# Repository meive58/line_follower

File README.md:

# Seguidor de Linha com ESP32

Projeto de robô seguidor de linha utilizando ESP32, sensores QTR-8 Digital, giroscópio MPU-6050 e encoders para motores N20.

## Componentes Utilizados

| Componente | Descrição |
|------------|-----------|
| ESP32 DevKit | Microcontrolador principal |
| QTR-8RC/QTR-8A | Array de 8 sensores infravermelhos para detecção de linha |
| MPU-6050 | Giroscópio e acelerômetro 6-DOF |
| Motor N20 com Encoder | Micro motor DC com encoder de quadratura |
| Ponte H (L298N/TB6612/DRV8833) | Driver para controle dos motores |

## Estrutura do Projeto

```
line_follower/
├── include/
│   └── pin_config.h        # Configuração de pinos (EDITE AQUI!)
├── lib/
│   ├── Encoder/
│   │   ├── encoder.h
│   │   └── encoder.cpp
│   ├── MotorDriver/
│   │   ├── motor_driver.h
│   │   └── motor_driver.cpp
│   ├── MPU6050/
│   │   ├── mpu6050.h
│   │   └── mpu6050.cpp
│   ├── PIDController/
│   │   ├── pid_controller.h
│   │   └── pid_controller.cpp
│   └── QTRSensor/
│       ├── qtr_sensor.h
│       └── qtr_sensor.cpp
├── src/
│   └── main.cpp            # Código principal
├── platformio.ini          # Configuração do PlatformIO
└── README.md               # Este arquivo
```

## Configuração dos Pinos

**IMPORTANTE**: Antes de compilar, edite o arquivo `include/pin_config.h` com os pinos que você escolher.

### Pinos Disponíveis no ESP32

| Pino | Recomendação |
|------|--------------|
| GPIO 0 | Evite (boot mode) |
| GPIO 1 | Evite (TX0 - debug serial) |
| GPIO 2 | LED onboard - pode usar |
| GPIO 3 | Evite (RX0 - debug serial) |
| GPIO 4 | Seguro |
| GPIO 5 | Seguro |
| **GPIO 6-11** | **NÃO USAR (flash interna)** |
| GPIO 12-33 | Seguros para uso geral |
| GPIO 34-39 | Apenas entrada (sem pull-up) |

### Exemplo de Configuração

```c
// Sensor QTR-8 (8 pinos GPIO)
#define QTR_SENSOR_0    32
#define QTR_SENSOR_1    33
#define QTR_SENSOR_2    25
#define QTR_SENSOR_3    26
#define QTR_SENSOR_4    27
#define QTR_SENSOR_5    14
#define QTR_SENSOR_6    12
#define QTR_SENSOR_7    13

// MPU-6050 (I2C)
#define MPU_SDA_PIN     21
#define MPU_SCL_PIN     22

// Encoders (4 pinos com suporte a interrupção)
#define ENCODER_LEFT_A  34
#define ENCODER_LEFT_B  35
#define ENCODER_RIGHT_A 36
#define ENCODER_RIGHT_B 39

// Motores (6 pinos)
#define MOTOR_LEFT_EN   4
#define MOTOR_LEFT_IN1  16
#define MOTOR_LEFT_IN2  17
#define MOTOR_RIGHT_EN  5
#define MOTOR_RIGHT_IN1 18
#define MOTOR_RIGHT_IN2 19

// Botões
#define BUTTON_START    23
#define BUTTON_CALIB    15
```

## Instalação

### Pré-requisitos

1. [Visual Studio Code](https://code.visualstudio.com/)
2. [Extensão PlatformIO](https://platformio.org/install/ide?install=vscode)

### Compilação e Upload

1. Abra a pasta `line_follower` no VS Code
2. Edite `include/pin_config.h` com seus pinos
3. Conecte o ESP32 via USB
4. Clique no botão "Upload" (→) na barra inferior do PlatformIO

## Uso

### Calibração

1. Ligue o robô e aguarde a inicialização
2. Pressione o botão **CALIB**
3. Mantenha o robô **imóvel** durante a calibração do giroscópio (~3s)
4. Mova o robô sobre a linha (preto e branco) por ~10 segundos
5. A calibração será salva automaticamente

### Execução

1. Posicione o robô sobre a linha
2. Pressione o botão **START**
3. Aguarde a contagem regressiva (3, 2, 1...)
4. O robô começará a seguir a linha

### LED de Status

| Estado | LED |
|--------|-----|
| Aguardando | Pisca lento (1Hz) |
| Calibrando | Aceso fixo |
| Seguindo | Aceso fixo |
| Linha perdida | Pisca rápido (10Hz) |

## Ajuste do PID

Os ganhos do PID estão definidos no arquivo `src/main.cpp`:

```c
#define PID_KP  0.1f    // Proporcional
#define PID_KI  0.0001f // Integral
#define PID_KD  0.5f    // Derivativo
```

### Guia de Ajuste

1. **Comece com Ki = 0, Kd = 0**
2. **Aumente Kp** até o robô oscilar levemente
3. **Aumente Kd** para reduzir a oscilação
4. **Adicione Ki** (pequeno) se houver erro persistente

### Valores Sugeridos para Início

| Pista | Kp | Ki | Kd |
|-------|----|----|----| 
| Iniciante (curvas suaves) | 0.05 | 0.0001 | 0.3 |
| Intermediário | 0.1 | 0.0002 | 0.5 |
| Avançado (curvas fechadas) | 0.15 | 0.0005 | 0.8 |

## Diagrama de Conexões

```
                    ┌─────────────────┐
                    │     ESP32       │
                    └─────────────────┘
                            │
        ┌───────────────────┼───────────────────┐
        │                   │                   │
        ▼                   ▼                   ▼
┌───────────────┐   ┌───────────────┐   ┌───────────────┐
│   QTR-8       │   │   MPU-6050    │   │   Ponte H     │
│   (8 pinos)   │   │   (I2C)       │   │   (6 pinos)   │
└───────────────┘   └───────────────┘   └───────────────┘
                                                │
                                        ┌───────┴───────┐
                                        │               │
                                        ▼               ▼
                                ┌───────────┐   ┌───────────┐
                                │ Motor E   │   │ Motor D   │
                                │ + Encoder │   │ + Encoder │
                                └───────────┘   └───────────┘
```

## API dos Módulos

### QTRSensorArray

```cpp
void calibrate();                    // Calibra os sensores
uint16_t readLinePosition();         // Retorna posição (0-7000)
int16_t getError();                  // Retorna erro (-3500 a +3500)
bool isLineLost();                   // Verifica se perdeu a linha
bool detectCrossing();               // Detecta cruzamento
```

### MPU6050Sensor

```cpp
void calibrateGyro(uint16_t samples); // Calibra o giroscópio
void update();                        // Atualiza ângulos (chamar no loop)
float getYaw();                       // Retorna ângulo yaw em graus
void resetYaw();                      // Reseta yaw para zero
```

### Encoder

```cpp
long getCount();                     // Retorna contagem de pulsos
float getRPM();                      // Retorna velocidade em RPM
float getDistance(float diameter);   // Retorna distância percorrida
void resetCount();                   // Reseta contador
```

### MotorDriver

```cpp
void setSpeeds(int16_t left, int16_t right);  // Define velocidades
void forward(uint8_t speed);                   // Move para frente
void brake();                                  // Freia os motores
```

## Solução de Problemas

| Problema | Solução |
|----------|---------|
| ESP32 não conecta | Verifique o driver USB (CP210x ou CH340) |
| Sensores não calibram | Verifique as conexões e alimentação |
| Robô não segue a linha | Recalibre em ambiente adequado (iluminação constante) |
| Robô oscila muito | Reduza Kp ou aumente Kd |
| Robô perde a linha nas curvas | Aumente a velocidade base ou ajuste Kp |
| Motores não funcionam | Verifique alimentação da ponte H |

## Licença

Este projeto é livre para uso educacional.

## Autor

Desenvolvido como projeto de TCC.

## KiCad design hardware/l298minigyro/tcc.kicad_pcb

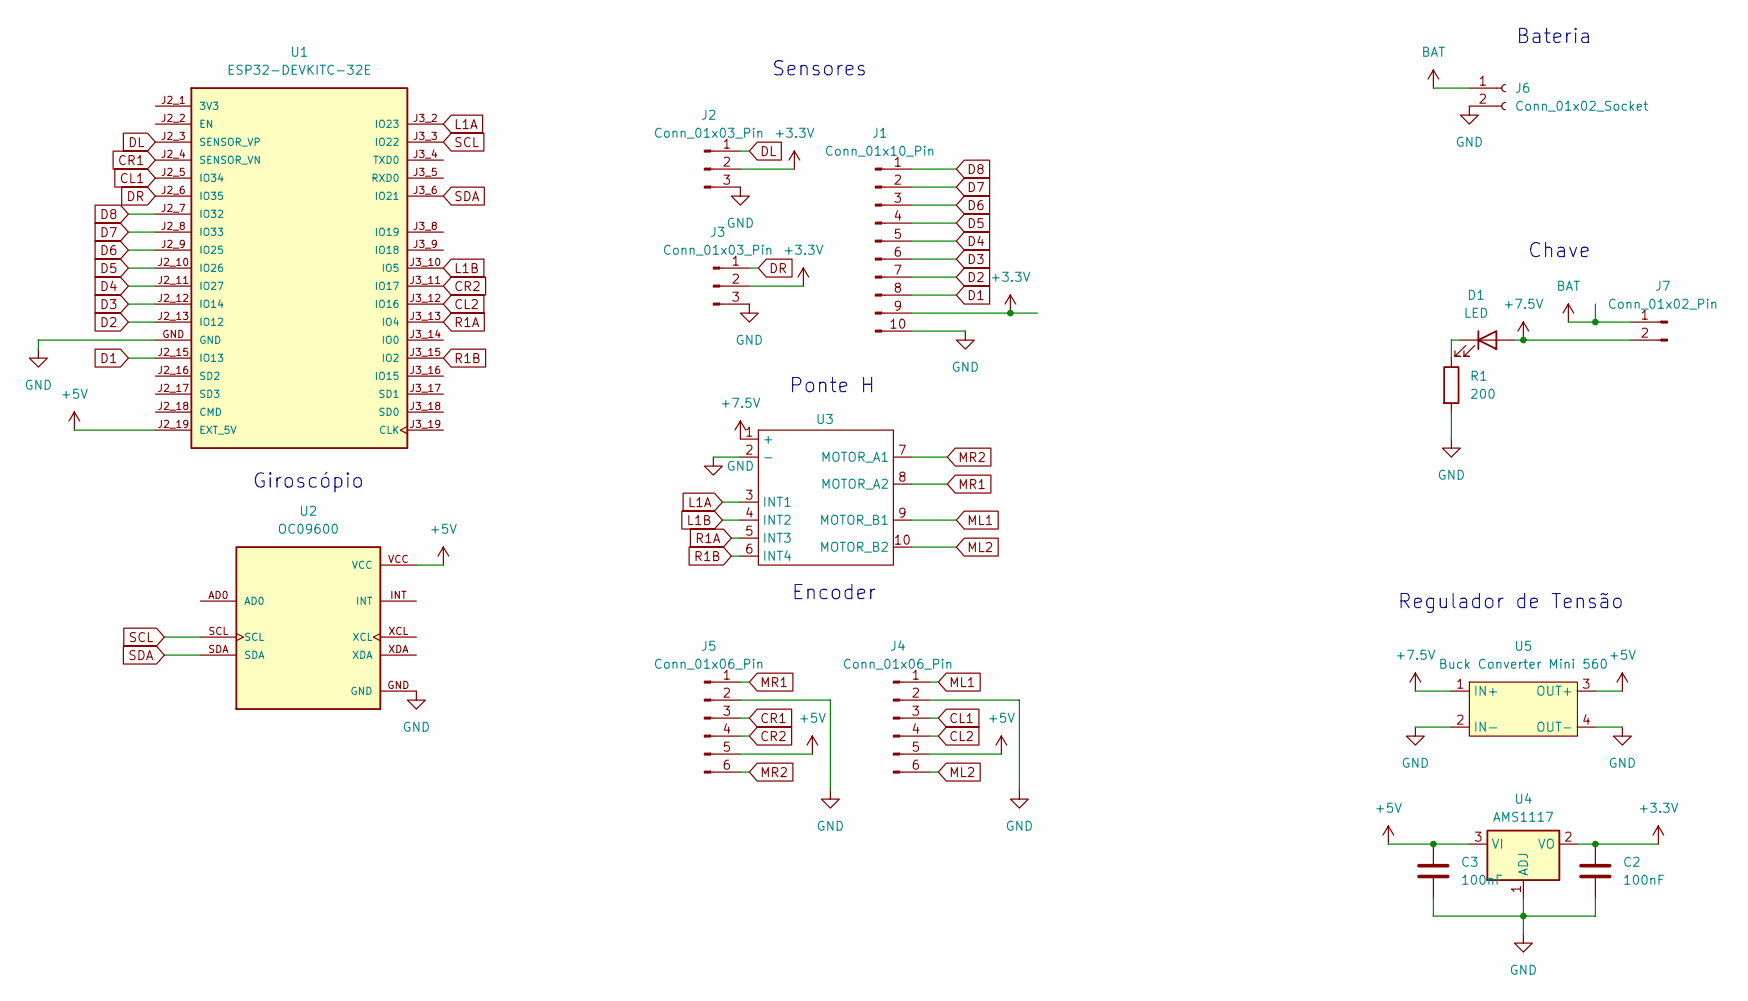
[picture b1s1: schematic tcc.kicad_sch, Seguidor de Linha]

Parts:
C2, C3: 100nF; C_Disc_D4.7mm_W2.5mm_P5.00mm
D1: LED; LED_D5.0mm
J1: Conn_01x10_Pin; PinHeader_1x10_P2.54mm_Vertical
J2, J3: Conn_01x03_Pin; PinHeader_1x03_P2.54mm_Vertical
J4, J5: Conn_01x06_Pin; JST_PH_B6B-PH-K_1x06_P2.00mm_Vertical
J6: Conn_01x02_Socket; PinSocket_1x02_P1.27mm_Vertical_SMD_Pin1Left
J7: Conn_01x02_Pin; PinHeader_1x02_P2.54mm_Vertical
R1: 200; R_Axial_DIN0204_L3.6mm_D1.6mm_P7.62mm_Horizontal
U1: ESP32-DEVKITC-32E; MODULE_ESP32-DEVKITC-32E; PARTREV 1.4
U2: OC09600; MODULE_OC09600; PARTREV NA
U3: H-Bridge-MX1616-Module
U4: AMS1117; SOT-223-3_TabPin2
U5: Buck Converter Mini 560; Mini_560

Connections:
+3.3V: C2.1, J1.9, J2.2, J3.2, U4.2 (VO)
+5V: C3.1, J4.5, J5.5, U1.J2_19 (EXT_5V), U2.VCC, U4.3 (VI), U5.3 (OUT+)
+7.5V: D1.2 (A), J7.2, U3.1 (+), U5.1 (IN+)
BAT: J6.1, J7.1
CL1: J4.3, U1.J2_5 (IO34)
CL2: J4.4, U1.J3_12 (IO16)
CR1: J5.3, U1.J2_4 (SENSOR_VN)
CR2: J5.4, U1.J3_11 (IO17)
D1: J1.8, U1.J2_15 (IO13)
D2: J1.7, U1.J2_13 (IO12)
D3: J1.6, U1.J2_12 (IO14)
D4: J1.5, U1.J2_11 (IO27)
D5: J1.4, U1.J2_10 (IO26)
D6: J1.3, U1.J2_9 (IO25)
D7: J1.2, U1.J2_8 (IO33)
D8: J1.1, U1.J2_7 (IO32)
DL: J2.1, U1.J2_3 (SENSOR_VP)
DR: J3.1, U1.J2_6 (IO35)
GND: C2.2, C3.2, J1.10, J2.3, J3.3, J4.2, J5.2, J6.2, R1.2, U1.GND, U2.GND, U3.2 (-), U4.1 (ADJ), U5.2 (IN-), U5.4 (OUT-)
L1A: U1.J3_2 (IO23), U3.3 (INT1)
L1B: U1.J3_10 (IO5), U3.4 (INT2)
ML1: J4.1, U3.9 (MOTOR_B1)
ML2: J4.6, U3.10 (MOTOR_B2)
MR1: J5.1, U3.8 (MOTOR_A2)
MR2: J5.6, U3.7 (MOTOR_A1)
unnamed: D1.1 (K), R1.1
R1A: U1.J3_13 (IO4), U3.5 (INT3)
R1B: U1.J3_15 (IO2), U3.6 (INT4)
SCL: U1.J3_3 (IO22), U2.SCL
SDA: U1.J3_6 (IO21), U2.SDA

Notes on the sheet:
Encoder
Regulador de Tensão
Sensores
Chave
Giroscópio
Bateria
Ponte H

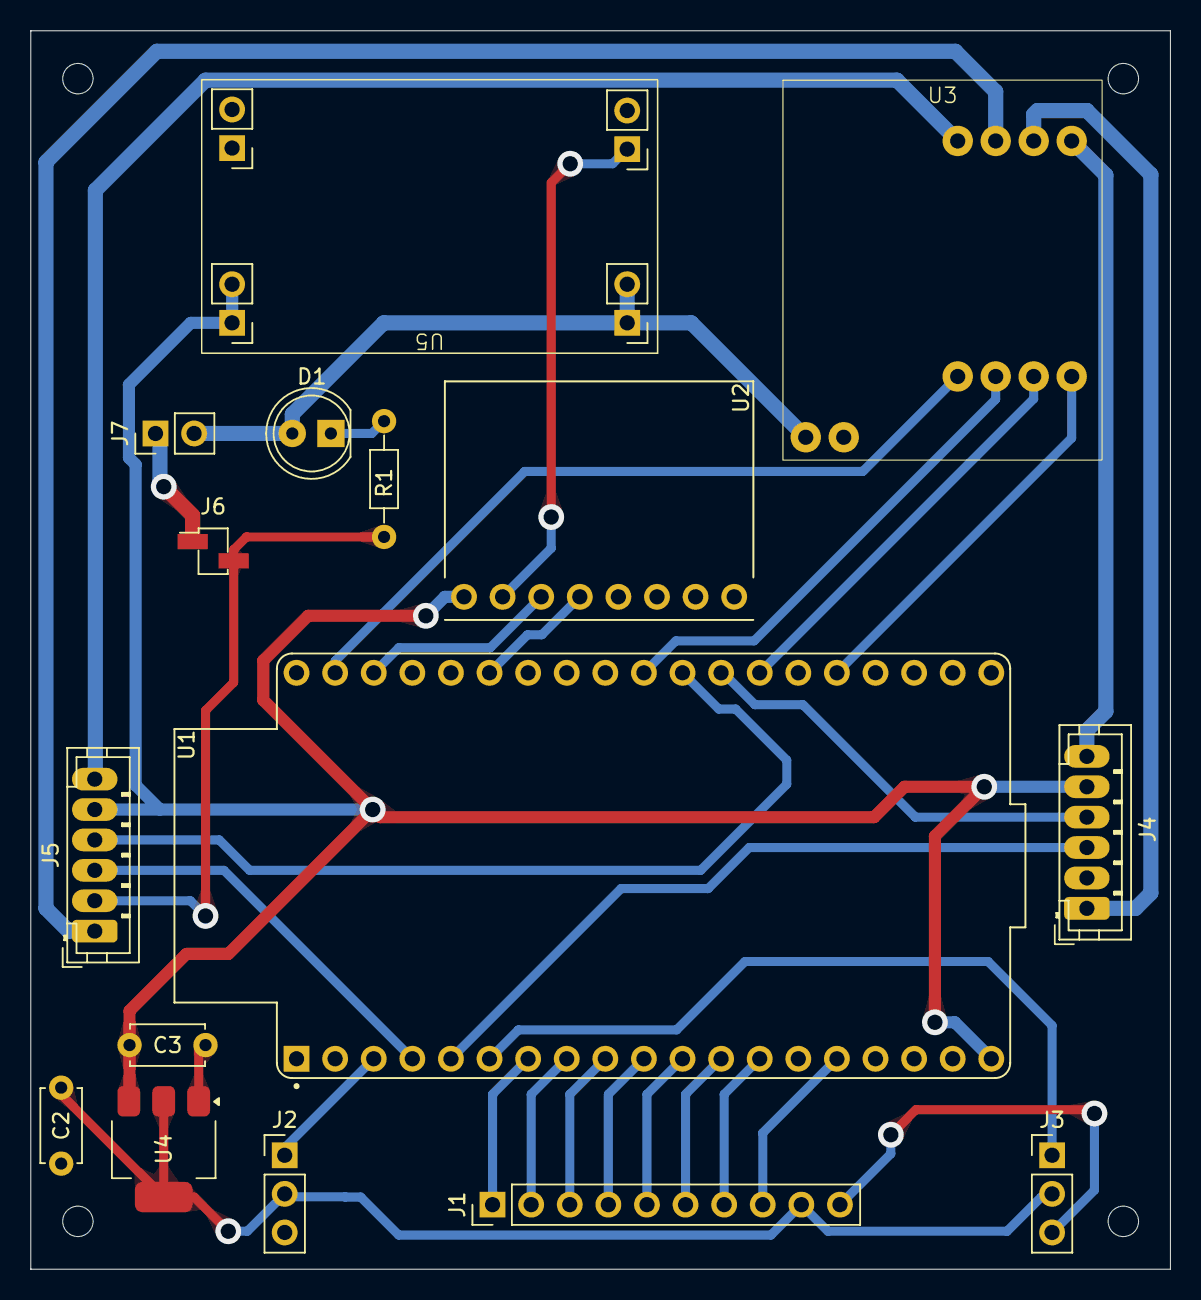
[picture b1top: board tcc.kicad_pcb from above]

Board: 2 copper layers, 75.0 x 81.5 mm, 16 parts (0 on the bottom side), 30 nets.

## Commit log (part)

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2026-02-26 tudo, primeira tentativa
2026-03-08 Update pin configuration and test qtr sensors and mpu
2026-03-08 motores com ponte h l9110s
2026-03-08 comentando encoder na main
2026-03-10 adicionando comandos bluetooth para start e calibracao
